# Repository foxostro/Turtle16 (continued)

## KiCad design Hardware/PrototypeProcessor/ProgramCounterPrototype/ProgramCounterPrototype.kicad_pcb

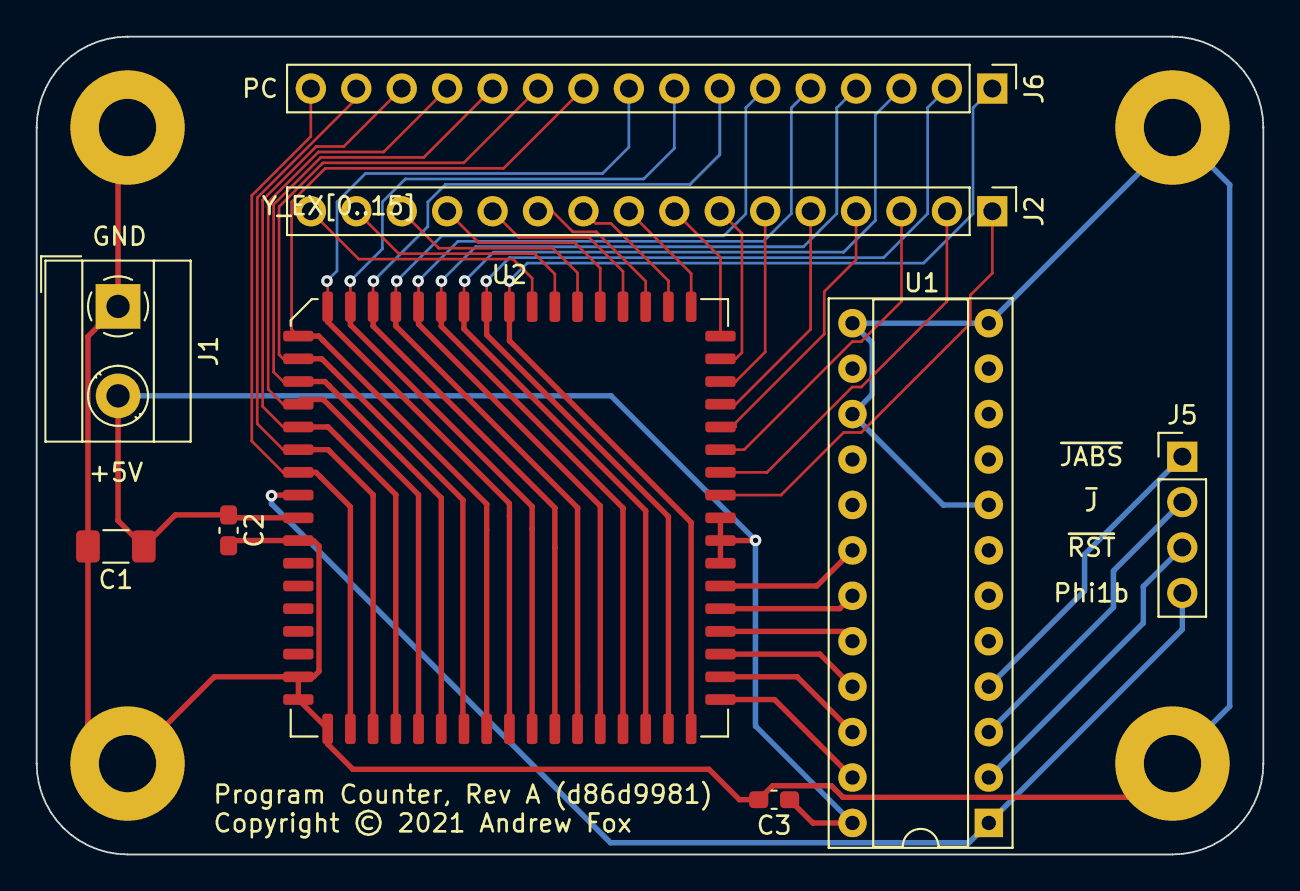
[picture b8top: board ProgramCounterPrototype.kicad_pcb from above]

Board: 2 copper layers, 68.6 x 45.7 mm, 13 parts (0 on the bottom side), 44 nets.

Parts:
C1: 100µF; C_1206_3216Metric_Pad1.33x1.80mm_HandSolder
C2, C3: 100nF; C_0603_1608Metric_Pad1.08x0.95mm_HandSolder
H1, H2, H3, H4: MountingHole_Pad; MountingHole_3.2mm_M3_Pad
J1: Screw_Terminal_01x02; TerminalBlock_MetzConnect_Type055_RT01502HDWU_1x02_P5.00mm_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
J2: Y_EX[0..15]; PinHeader_1x16_P2.54mm_Vertical
J5: Ctl; PinHeader_1x04_P2.54mm_Vertical
J6: PC; PinHeader_1x16_P2.54mm_Vertical
U1: ATF22V10C-7PX; DIP-24_W7.62mm_Socket
U2: IDT7381; PLCC-68_24.2x24.2mm_P1.27mm

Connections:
/PC0: J6.1, U2.1, U2.43
/PC1: J6.2, U2.2, U2.42
/PC2: J6.3, U2.3, U2.41
/PC3: J6.4, U2.4, U2.40
/PC4: J6.5, U2.5, U2.39
/PC5: J6.6, U2.6, U2.38
/PC6: J6.7, U2.7, U2.37
/PC7: J6.8, U2.8, U2.36
/PC8: J6.9, U2.9, U2.35
/PC9: J6.10, U2.10, U2.34
/PC10: J6.11, U2.11, U2.33
/PC11: J6.12, U2.12, U2.32
/PC12: J6.13, U2.13, U2.31
/PC13: J6.14, U2.14, U2.30
/PC14: J6.15, U2.15, U2.29
/PC15: J6.16, U2.16, U2.28
/Y_EX0: J2.1, U2.53
/Y_EX1: J2.2, U2.54
/Y_EX2: J2.3, U2.55
/Y_EX3: J2.4, U2.56
/Y_EX4: J2.5, U2.57
/Y_EX5: J2.6, U2.58
/Y_EX6: J2.7, U2.59
/Y_EX7: J2.8, U2.60
/Y_EX8: J2.9, U2.61
/Y_EX9: J2.10, U2.62
/Y_EX10: J2.11, U2.63
/Y_EX11: J2.12, U2.64
/Y_EX12: J2.13, U2.65
/Y_EX13: J2.14, U2.66
/Y_EX14: J2.15, U2.67
/Y_EX15: J2.16, U2.68
/sheet606491AF/~JABS: J5.1, U1.4
/sheet606491AF/~J: J5.2, U1.3
/sheet606491AF/~RST: J5.3, U1.2
GND: C1.2, C2.2, C3.2, H1.1, H2.1, H3.1, H4.1, J1.1, U1.8, U1.12, U1.13, U1.15, U2.19, U2.25, U2.26, U2.27
unnamed: U1.18, U2.49
unnamed: U1.19, U2.48
unnamed: U1.20, U2.47
unnamed: U1.21, U2.46
unnamed: U1.22, U2.45
unnamed: U1.23, U2.44
Phi1b: J5.4, U1.1, U2.17
VCC: C1.1, C2.1, C3.1, J1.2, U1.24, U2.18, U2.50, U2.51, U2.52
